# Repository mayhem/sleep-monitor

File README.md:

# sleep-monitor
A wearable sleep monitor to wake you in case you're sleeping badly

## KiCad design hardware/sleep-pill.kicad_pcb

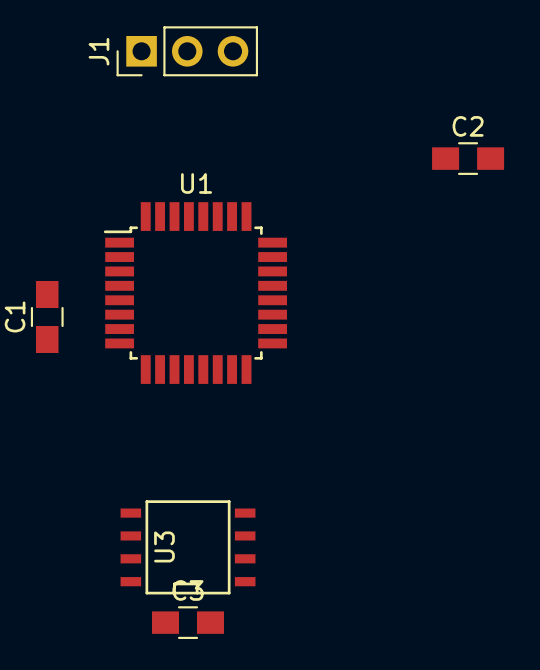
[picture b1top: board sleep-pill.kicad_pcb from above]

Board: 2 copper layers, 6 parts (0 on the bottom side), 9 nets, no tracks yet.

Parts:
C1, C2, C3: 100nF; C_0805_HandSoldering
J1: Serial; Pin_Header_Straight_1x03_Pitch2.54mm
U1: ATMEGA328P-AU; TQFP-32_7x7mm_Pitch0.8mm
U3: 23LC1024; SOIC-8-N

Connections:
/CS: U1.14, U3.1
/MISO: U1.16, U3.2
/MOSI: U1.15, U3.5
/RX: J1.1, U1.30
/SCK: U1.17, U3.6
/TX: J1.2, U1.31
/VCC: C1.1, C3.1, U3.8
GND: C1.2, C2.2, C3.2, J1.3, U1.3, U1.5, U1.21, U3.4
unnamed: C2.1, U1.4, U1.6, U1.18
